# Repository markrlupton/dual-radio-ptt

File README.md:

# Dual-Radio PTT Audio Board (Teensy 4.0): rev C.2

A carrier for a Teensy 4.0 that bridges a headset to two tactical radios. A front-panel daughterboard carries four encoders, the PTT buttons and the LEDs.

Rev C.2 is the manufacturing close-out after the fourth outside review (of rev C.1). That review found no new electrical problem, so **the copper and the circuit are unchanged from C.1** apart from the courtyard fix. This revision covers parts selection, the project footprint library and the fab and assembly files. The full spec is at https://claude.ai/artifact/69VW2KktqLnx2tKRjk1YQv ; its "Rev C", "Rev C.1" and "Rev C.2" sections list every change.

| Board | Size | Stack | Parts | Status |
|---|---|---|---|---|
| `radio_carrier` | 65 × 95 mm | F sig + GND / In1 solid GND / In2 +5.2 V plane (low-current rails and a few codec-area signals) / B sig + GND | 240 | Fully routed. DRC (KiCad 7.0.11): **0 copper, 0 courtyard, 0 unconnected, 0 footprint/library** issues. Only silkscreen warnings are left (silk clipped by mask or overlapping, which JLC clips anyway). ERC: 0 errors, 0 warnings. |
| `radio_frontpanel` | 124 × 38 mm | 4 layers (both inner layers GND) | 54 | Layout unchanged from rev B. DRC: same result as the carrier (silkscreen warnings only). ERC: 0 errors, 0 warnings. |

Vias are 0.45 mm with a 0.2 mm drill on the carrier and 0.5 / 0.25 mm on the front panel. Order the carrier with the **JLC04161H-7628** stack-up and **impedance control** (see below).

## What changed in rev C.2 (fourth review)
| Review item | Rev C.2 |
|---|---|
| **LCSC selections must keep the specified tolerances** (selecting by value and package alone is not enough) | Every SMT row on both boards now has a specific MPN **and** LCSC number, chosen together, in the schematic (`MPN` and `LCSC` fields), both BOMs and the JLC BOM. Precision parts: **15 kΩ 0.1 % 25 ppm** Yageo RT0603BRD0715KL **C326733**; **11 kΩ 0.1 % 25 ppm** FH TD03G1102BT **C667038** (alt Yageo RT0603BRD0711KL); 20 kΩ / 4.99 kΩ 0.1 % unchanged (C723637 / C723532). Rev C.1's note that LCSC lacked 0.1 % 15 k / 11 k was wrong. The JLC BOM's Comment column is now the MPN, so JLC matches on part number, not value. See the selection table below. |
| **A real dielectric error turned up** | The generic 1 nF entry pointed at **C21122, an X7R part**, while C24, C32–C34 and C42–C44 are specified C0G (mic and ADC RF filters, TX low-pass). They are now FH 0603CG102J500NT **C1636** (C0G 50 V 5 %). The generator now refuses to emit a C0G capacitor without a C0G part selected, so this can't recur. |
| **Five power-stage courtyard overlaps** | Fixed: C103 / C104 moved 0.45 mm and C105 / C106 0.3 mm with their tracks. DRC now reports no courtyard overlaps. Switching-loop geometry is effectively unchanged. |
| **Footprint-library warning (codec footprint)** | Every footprint on both boards is now in a **project library** `radio.pretty` with its own `fp-lib-table`. That is 33 footprints on the carrier and 10 on the front panel, U1's HTQFP-64 thermal-via footprint included. All FPIDs in the PCB and all schematic `Footprint` fields point to `radio:<name>`. The library copies were checked pad-for-pad against what is placed on the boards (`mkfplib.py` asserts it). The project no longer depends on the installed KiCad library version; KiCad 8–10 renamed or revised several of these footprints. 3D models still reference the KiCad stock model path, which affects only the 3D view. |
| PCB ↔ schematic link | The PCB footprints now carry their schematic symbols' UUIDs (`relink.py`), so Update-PCB-from-Schematic sees a linked design without "re-link by reference". |
| **Controlled impedance** | Confirmed what we can confirm here: all three pairs are 0.30 mm / 0.20 mm gap on F.Cu only, no vias, over solid In1 GND. Lengths 39.9 / 39.7, 41.5 / 41.3 and 13.5 / 10.1 mm. Computed **89.3 Ω differential with mask** (εr 4.4), 95.9 Ω bare. **Order "Impedance control: yes" with JLC04161H-7628** and put in the order remark: *USB D+/D− pairs (nets USB_A_*, USB_B_*, USBH_*): 90 Ω ±10 % differential, L1 referenced to L2, 0.30 mm trace / 0.20 mm gap.* JLC may adjust width by a few µm to hit target; accept that. Only JLC's coupon measurement confirms the number. |
| **Host cable arrangement** | Stated explicitly under "Things you must do" (item 2) with J3's pinout. The pigtail is the one uncontrolled-impedance section of the high-speed path. |
| **Fab and assembly review** | Gerbers (4 Cu, paste, mask, silk, edge), separate PTH / NPTH Excellon and the job file were regenerated from the C.2 boards. **CPL rotations:** the JLC corrections for KiCad stock footprints are applied: SOT-23/-5/-6 +180°, SOIC / SOP / TSSOP +270°, VQFN-16 +270°. **`*_rotation_check.csv` lists every polarized part** with its KiCad angle, offset, final CPL angle and what to look at for pin 1. Packages the table doesn't cover are left at KiCad's angle and flagged: U1 HTQFP-64, U4 / U11 PVSON-10, U5 SSOP-28, U12 WSON-12, U15 X2QFN-12, Y1, the LEDs, the SOD diodes, J10–J12, J15, SW1. **Check every flagged part in JLC's placement preview before releasing the order**; their preview is the authority because it uses their own footprint for each LCSC part. All parts are top-side. |
| Substitutions | Leave JLC's automatic substitution off. If a part goes out of stock, pick a replacement from the alternates in the MPN field or one of the same tolerance / TCR / dielectric. Never substitute a 0.1 % resistor with a 1 % one, or a C0G with an X7R. |

### Parts chosen in rev C.2 (previously unselected or generic)
| Ref | Value / spec | MPN | LCSC |
|---|---|---|---|
| R70 R72 R75 R77 | 15 kΩ 0.1 % 25 ppm | Yageo RT0603BRD0715KL | C326733 |
| R71 R73 R76 R78 | 11 kΩ 0.1 % 25 ppm | FH TD03G1102BT (alt Yageo RT0603BRD0711KL) | C667038 |
| R116 R117 | 45.3 kΩ 1 % (current limit) | Viking ARG03FTC4532 (thin film, 25 ppm; alt Bourns CR0603-FX-4532ELF C49675646) | C218038 |
| R24 | 169 Ω 1 % (INA217 gain) | Panasonic ERJ-3EKF1690V | C403019 |
| R120 | 910 kΩ 1 % (TUSB321 VBUS_DET) | Bourns CR0603-FX-9103ELF (alt RESI AECR0603F910KK9 C352285) | C203887 |
| R122 | 1.24 kΩ 1 % (BQ24074 ILIM) | Vishay CRCW06031K24FKEA (alt FH RS-03K1241FT C321702) | C843923 |
| R127 | 422 kΩ 1 % (boost FB) | RALEC RTT034223FTP | C103627 |
| R129 | 294 kΩ 1 % (charge-pump FB+) | RALEC RTT032943FTP (alt Vishay CRCW0603294KFKEA C2092132) | C13177 |
| R131 | 287 kΩ 1 % (charge-pump FB−) | LIZ CR0603FA2873G | C100934 |
| C24 C32–C34 C42–C44 | 1 nF C0G | FH 0603CG102J500NT (alt Samsung CL10C102JB8NNNC C163508) | C1636 |
| C29 | 2.7 nF C0G | Walsin 0603N272J500CT | C388043 |
| C60–C63 | 330 pF C0G | Samsung CL10C331JB8NNNC | C1664 |
| C120 | 18 pF C0G | Samsung CL10C180JB8NNNC | C1647 |
| C80 C81 (DNP) | 10 pF C0G | Samsung CL10C100JB8NNNC | C1634 |
| Y1 | 12 MHz 3225, 20 pF, ±10 ppm | YXC X322512MSB4SI | C9002 |
| Front panel D3 | amber / orange 0805 | NationStar NCD0805O1 (605 nm) | C84262 |
| J10 J11 / J12 | JST GH 10 / 6 | BM10B-GHS-TBT / BM06B-GHS-TBT | C2983879 / C189892 |
| J15, SW1, ENC1–4 | USB-C, slide switch, encoders | GCT USB4125-GF-A-0190, C&K PCM12SMTR, Bourns PEC12R-4217F-S0024 | C5246813, C221841, C49671241 |

Rows still without an LCSC number are hand-soldered commodity mechanicals: 1×14 sockets, 1×3 / 2×8 headers, Micro-Fit 43650-0315 and the tactile switches. They are in the JLC BOM so you can mark them DNP. Stock moves; re-check availability in JLC's BOM tool when you order.

## What changed in rev C.1 (third review)
| Review item | Rev C.1 |
|---|---|
| **Battery current path had a 0.2 mm via and a 0.15 mm section feeding U10's BAT pins** | U10 (BQ24074) is turned 180° so its BAT pins face J16 and its OUT pins face the boost stage. **Both high-current paths are now single F.Cu copper pours with no vias:** J16 pin 1 → U10 BAT (narrowest about 1.55 mm along the run, about 1.05 mm only where the copper meets the 0.5 mm-pitch QFN pins) and U10 OUT → L1 / C103 / C104 / U11 VIN (narrowest about 1.1 mm, about 0.95 mm at the pin row). Other nets are kept out of both pours by the router, and no via of any net may sit within about 0.5 mm of their edges. C102 (battery cap) now sits on the battery pour under J16; C100 (IN cap) sits right under U10's IN pin; C101 moved near SW1. |
| USB-C input path | VBUS_IN (≤1.3 A) runs 0.5 mm (one 0.25 mm neck at the A9 pin between the CC pins). Each layer change uses two vias in parallel: two 0.6/0.3 mm vias going down, one 0.6/0.3 mm plus one 0.5/0.25 mm via coming up at U10's IN pin. Power-net vias are 0.6/0.3 mm wherever they fit. |
| **J16 pin 2 (battery −) thermal relief: 1 spoke where 2 are required** | J16, U10, C101 and C102 ground pads now connect solidly to the pours (no thermal relief). |
| **Current limit did not guarantee 500 mA with a 1 % resistor** | R116 / R117 → **45.3 kΩ 1 %**. TI's equations with the resistor tolerance included give **0.519 A minimum (R +1 %)** and **0.644 A maximum (R −1 %)** per port. 47.5 kΩ gave 0.494–0.616 A. |
| Host USB pair had 0.15 mm segments | Those were pad-entry stubs inside J3's 1.7 mm pads; they are now 0.30 mm like the rest of the pair. The pair's breakout into J3 is still uncoupled over the 2.54 mm pin pitch. |
| **"About 93 Ω under mask" was not what the solver modelled** | `zdiff.py --mask` now models the solder mask with JLCPCB's figures (1.2 mil on laminate and between traces, 0.6 mil on copper, εr 3.8) and 1.6 mil finished outer copper. 0.30 / 0.20 mm on the 0.2104 mm 7628 prepreg: **95.9 Ω bare, 89.3 Ω with mask** (εr 4.4), 94.3 / 87.9 Ω at εr 4.6. Rectangular trace cross-section; trapezoidal etching raises it slightly. Have JLC confirm with impedance control ordered. |
| **ERC not clean** | KiCad's own ERC (7.0.11, run in the schematic editor) now reports **0 errors and 0 warnings on both boards**. Fixes: PWR_FLAGs only on nets nothing else drives (GND, VBUS_IN, +5V_TEENSY), U11's second VOUT pin made passive, LM27762 PGOOD tied to GND as its datasheet says for unused (pin typed passive), PCM3168A pin 44 typed as the input it is in I²C mode, no stray no-connect flags, a project symbol library (`lib.kicad_sym` + `sym-lib-table`) so no library warnings. Reports: `*-erc.rpt`. Newer KiCad versions add checks; I could not run KiCad 10 here. |
| LCSC numbers | Added: TPS61230DRCR C139626, NCP163ASN500T1G C603657, TUSB321RWBR C139392, PESD5V0L1BA C85380, SMF15CA C2890424, L1 → XAL4020-102MEC C4555951 (current version of the -MEB), RT0603BRD0720KL C723637, RT0603BRD074K99L C723532. |

## What changed from rev B (rev C)
| Review item | Rev C |
|---|---|
| **U6 / U7 enable polarity wrong** (TPS2051B is active-high; the hub's PWRJ is active-low) | Replaced with **TPS2552DBVR**: active-low EN, open-drain FAULT, adjustable current limit. EN ← HUB_PWRJ, FAULT → HUB_OVC (wired-OR). |
| Port current limit 0.75–1.25 A per port (TPS2051B) | R116 / R117 on ILIM set the limit (rev C.1: 45.3 kΩ, **0.519–0.644 A per port** including the 1 % tolerance). Two shorted ports can't pull more than about 1.3 A from +5V2. |
| **J16 JST-PH (2 A) on a 2.6 A battery path** | **Molex Micro-Fit 3.0 43650-0315** vertical (5 A per contact): 1 +, 2 −, 3 NTC. Mating housing 43645-0300 with 43030 crimps. |
| Battery / SYS copper | Superseded in rev C.1 by the battery and SYS pours above. |
| **USB pairs not coupled / not single-layer** | All three pairs re-routed **on F.Cu only, no vias, one width**: 0.30 mm traces, 0.20 mm gap (0.50 mm pitch) over the solid In1 GND, routed as a true pair (one centreline, both conductors offset from it). Impedance: see the rev C.1 table (89 Ω with mask modelled, target 90 Ω). Measured lengths: radio A 39.9 / 39.7 mm, radio B 41.5 / 41.3 mm (0.2 mm skew); host link 13.5 / 10.1 mm (set by J3's 2.54 mm pin spacing). |
| Pair topology | To route both radio pairs without crossing, the hub ports were swapped (radio A now on FE1.1s port 2, pins 8 / 9; radio B on port 1, pins 10 / 11) and U8 / U9 were turned 180° so each pair flows straight through its USBLC6 (pins 1→6 and 3→4) before dropping into the connector. The ESD ground pin gets its own via under the part. |
| Continuous load vs. 1.3 A USB input | Operating-mode table below. At full load on USB the battery supplements; this is intentional and stated. |
| PTT TVS (SMF15CA, 15 V standoff) | Maximum radio PTT keying voltage is now a stated limit: **≤ 15 V open-circuit**. |
| Port power cycling | Documented: the hub's power switching is ganged, so a power-cycle drops **both** radio ports. |

## Operating modes and power budget
Loads at the +5.2 V boost output: board ≈ 350 mA (1.8 W); each radio port 0–500 mA nominal, current-limited at 0.519 A min / 0.644 A max.

| Mode | Input available | Full load (board + 2 × 500 mA ≈ 7 W out, ≈ 7.8 W in) | Board only (≈ 2 W in) |
|---|---|---|---|
| Battery only | 18650, 3.0–4.2 V | ≈ 2.2 A from the cell at 3.6 V, ≈ 2.6 A at 3.0 V. Use a cell rated ≥ 5 A continuous. | ≈ 0.6 A from the cell |
| USB-C, source offers ≥ 1.5 A (TUSB321 → 1.3 A input limit) | ≈ 6 W | Input covers most of it; the battery supplies the rest (BQ24074 supplement mode). The cell slowly discharges. | Fully covered; battery charges |
| USB-C, default 500 mA source | ≈ 2.5 W | Battery supplies ≈ 5 W; net discharge | Covered, little or no charge current |
| Fault: both ports shorted | — | ≤ 2 × 0.644 A ≈ 6.7 W + board ≈ 8.5 W out, ≈ 9.7 W in → ≤ 3.2 A from the cell at 3.0 V (2.7 A at 3.6 V). Within the TPS61230 (4 A valley), BQ24074 battery FET (4.5 A) and Micro-Fit (5 A) ratings, and carried by the no-via battery/SYS pours. The TPS2552s thermally cycle into a hard short and report FAULT to the hub. | — |

**Without a battery fitted, full radio-port load on USB alone is not supported.**

## Things you must do
1. **Cut the Teensy VUSB–VIN pad.**
2. **USB host pigtail (J3).** J3 pin 1 = D+ (USBH_DP), pin 2 = D− (USBH_DM), pin 3 = GND. Wire the Teensy 4.0's underside USB-host D+ / D− pads to J3 pins 1 / 2, and a Teensy GND pin to J3 pin 3. Use a twisted pair (about 1 twist per cm, **60 mm or less**, 28–30 AWG), with the GND wire twisted along with it or run right beside it. This hop carries the hub's high-speed upstream link (480 Mb/s). It is the only part of that path without controlled impedance, so keep it as short as the stack-up allows and don't route it past the boost inductor L1. If the hub shows enumeration errors, shorten the pigtail first.
3. **Firmware is not written yet.** Everything below is a requirement on firmware you still need to write:
   - Codec rate: set PCM3168A **SRAD = SRDA = 01 (single rate)**; auto mode reads 256 fs MCLK as dual rate. Set FMTAD / FMTDA to match the Teensy's TDM slot layout.
   - PTT safety: watchdog, transmit timeout, release PTT if I²C to the buttons stalls. The gate pull-downs only cover reset.
   - Headphone mute: HP_EN high only after the codec and rails are running; low before shutdown.
   - Port power: a stuck radio is recovered by the USB host toggling hub port power, which cycles both ports together.
4. **Battery.** Protected 18650 with a 10 kΩ NTC on J16 pin 3 (or fit R124, which disables temperature protection).
5. **Radios.** PTT line must be ≤ 15 V open-circuit and switched to ground. RX ≤ 2 Vrms differential line level (fit R34 / R54 for speaker level). TX is mic level; R40 / R60 (100 Ω) set the drive level and may need changing per radio. Compatibility with a specific radio is conditional on these until checked against its pinout.

## Codec channel map (TDM slots)
| Channel | Use |
|---|---|
| ADC1 | Aux in (J14 pins 9 / 10) |
| ADC2, ADC6 | Unused (terminated) |
| ADC3 | Headset mic (INA217, G ≈ 60) |
| ADC4 / ADC5 | Radio A / Radio B RX |
| DAC1 / DAC2 | Headset L / R (OPA1622) |
| DAC3 / DAC4 | Radio A / Radio B TX (OPA1678) |
| DAC5 | Aux out (J14 pins 13 / 14) |

## Teensy 4.0 pin map
| Pin | Signal | | Pin | Signal |
|---|---|---|---|---|
| 0 | EXP_0 (aux) | | 23 | MCLK |
| 1 | EXP_1 (aux) | | 22 | VBAT_SENSE (A8, ½ divider) |
| 2 | PTT_A drive | | 21 | BCLK |
| 3 | PTT_B drive | | 20 | FSYNC |
| 4 | IOX_INT (TCA9555) | | 19 / 18 | I²C SCL / SDA |
| 5 | CODEC_RST | | 17 / 16 | ENC Radio-A channel B / A |
| 6 | HP_EN | | 15 / 14 | ENC Radio-A volume B / A |
| 7 / 8 | TDM TX / RX | | 13 | EXP_13 (aux) |
| 9 / 10 | ENC Radio-B volume A / B | | VIN | +5 V via B5819W |
| 11 / 12 | ENC Radio-B channel A / B | | 3V3 | not used |

## Connectors
| Ref | Part | Pins |
|---|---|---|
| J10 / J11 | JST-GH 10 | 1 RX, 2 RX_RTN, 3 TX, 4 TX_RTN, 5 PTT (≤ 15 V), 6 PTT_RTN, 7 D+, 8 D−, 9 VBUS (switched, 0.519–0.644 A limit), 10 GND |
| J12 | JST-GH 6 | 1 MIC+, 2 MIC−, 3 SPK_L, 4 SPK_R, 5 GND, 6 shield |
| J13 | 2×8 1.27 mm | front-panel ribbon |
| J14 | 2×8 2.54 mm aux | +3V3, +5V2, EXP_0/1/13, ADC1±, DAC5±, GND |
| J15 | USB-C | power in (TUSB321 detects the source's current) |
| J16 | Molex Micro-Fit 3.0 43650-0315 | 1 +, 2 −, 3 NTC |
| J3 | 1×3 | USB host D+, D−, GND pigtail |

## Known limits
- **Ground isolation:** none. The radio ports share ground through J10 / J11 pin 10 and USB.
- **CPL rotations** for packages not in the standard correction table are KiCad's own angle; confirm them in JLC's placement preview (`*_rotation_check.csv`).
- **Moved parts:** C80 (DNP crystal load cap) moved 5 mm from the crystal to clear the USB corridor. Leave it unfitted (the FE1.1s has internal load capacitors). C94 (radio B VBUS bulk) moved next to U7.
- **USB impedance:** computed, not measured. Order impedance control and let JLC confirm.
- **Charge-status LED feed:** R125's VBUS_IN branch and the battery-voltage sense branch (VBAT to R9 / TP15) are thin tracks with single vias; they carry milliamps.

## Files
- `radio_carrier/` and `radio_frontpanel/`: KiCad 7 projects (open with KiCad 7 or newer) with their project symbol library (`lib.kicad_sym`, `sym-lib-table`), project footprint library (`radio.pretty`, `fp-lib-table`), and ERC / DRC reports.
- `*/fab/`: Gerbers and drill (zip), `*_BOM_JLC.csv`, `*_CPL_JLC.csv` (JLC rotation corrections applied), `*_rotation_check.csv`, `*_BOM_full.csv` (MPN, LCSC, fitted, SMT / hand-solder), schematic PDF.
- `img/`: renders.
- `scripts/`: generators, router and finishing scripts, `zdiff.py` impedance solver (`--mask`), `pourcheck.py` (narrowest copper on the power paths), `erc_gui.sh` (runs KiCad's ERC headless), `mkfplib.py` (builds the project footprint library and checks it against the boards), `relink.py` (PCB ↔ schematic UUID link).
- `img/carrier_power_paths.png`, `img/carrier_usb_pairs.png`: the power pours and the USB pairs.

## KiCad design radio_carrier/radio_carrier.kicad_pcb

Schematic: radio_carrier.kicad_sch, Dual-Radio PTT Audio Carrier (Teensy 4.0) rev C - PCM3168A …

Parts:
C1, C25, C26, C50, C51, C65, C66, C82, C84, C86, C88, C90, C93: 100nF; C_0603_1608Metric; MPN 0603 X7R 16V; LCSC C14663
C10, C11, C12, C13, C14, C15, C23, C28, C30, C31, C40, C41, C70, C71, C72, C109, C111, C115, C117, C118, C119: 1uF; C_0603_1608Metric; MPN 0603 X7R 16V; LCSC C15849
C16, C17, C18, C19, C20, C21, C22, C27, C35, C45, C67, C68, C83, C85, C87, C91, C94, C101, C102, C104, C110, C112: 10uF; C_0805_2012Metric; MPN 0805 X7R 16V; LCSC C15850
C24, C32, C33, C34, C42, C43, C44: 1nF; C_0603_1608Metric; MPN FH 0603CG102J500NT (C0G 50V 5%; alt Sam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; LCSC C1636
C29: 2.7nF; C_0603_1608Metric; MPN Walsin 0603N272J500CT (C0G 50V 5%); LCSC C388043
C60, C61, C62, C63: 330pF; C_0603_1608Metric; MPN Samsung CL10C331JB8NNNC (C0G 50V 5%); LCSC C1664
C80, C81: 10pF; C_0603_1608Metric; MPN Samsung CL10C100JB8NNNC (C0G 50V 5%); LCSC C1634; not fitted
C100, C116: 4.7uF; C_0805_2012Metric; MPN 0805 X7R 16V; LCSC C1779
C103, C105, C106, C107: 22uF; C_0805_2012Metric; MPN 0805 X7R 16V; LCSC C45783
C108: 10nF; C_0603_1608Metric; MPN 0603 X7R 16V; LCSC C57112
C113, C114: 2.2uF; C_0603_1608Metric; MPN 0603 X7R 16V; LCSC C23630
C120: 18pF; C_0603_1608Metric; MPN Samsung CL10C180JB8NNNC (C0G 50V 5%); LCSC C1647
D1: B5819W; D_SOD-123; MPN B5819W Schottky 1 A 40 V; LCSC C8598
D2, D3: BAV99; SOT-23; MPN BAV99 dual diode; LCSC C2500
D10, D11, D12, D20, D21, D22: PESD5V0L1BA; D_SOD-323; MPN Nexperia PESD5V0L1BA bidirectional; LCSC C85380
D13, D23: SMF15CA; D_SOD-123F; MPN SMF15CA bidirectional TVS (VRWM 15 V, V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; LCSC C2890424
D30: SMF5.0A; D_SOD-123F; MPN SMF5.0A TVS 5 V; LCSC C78395
D31: RED; LED_0805_2012Metric; MPN 0805 red LED; LCSC C84256
D32: GREEN; LED_0805_2012Metric; MPN 0805 green LED; LCSC C2297
H1, H2, H3, H4: M2.5; MountingHole_2.7mm_M2.5
J1: Teensy 4.0 left (GND,0..12); PinSocket_1x14_P2.54mm_Vertical; MPN 1x14 2.54 mm female socket
J2: Teensy 4.0 right (VIN,GND,3V3,23..13); PinSocket_1x14_P2.54mm_Vertical; MPN 1x14 2.54 mm female socket
J3: USB HOST (wire to Teensy pads); PinHeader_1x03_P2.54mm_Vertical; MPN 1x3 2.54 mm header
J10: RADIO A (JST-GH 10); JST_GH_BM10B-GHS-TBT_1x10-1MP_P1.25mm_Vertical; MPN JST BM10B-GHS-TBT; LCSC C2983879
J11: RADIO B (JST-GH 10); JST_GH_BM10B-GHS-TBT_1x10-1MP_P1.25mm_Vertical; MPN JST BM10B-GHS-TBT; LCSC C2983879
J12: HEADSET (JST-GH 6); JST_GH_BM06B-GHS-TBT_1x06-1MP_P1.25mm_Vertical; MPN JST BM06B-GHS-TBT; LCSC C189892
J13: FRONT PANEL (2x8 1.27); PinHeader_2x08_P1.27mm_Vertical; MPN 2x8 1.27 mm header
J14: AUX (2x8 2.54); PinHeader_2x08_P2.54mm_Vertical; MPN 2x8 2.54 mm header
J15: USB-C 5V IN; USB_C_Receptacle_GCT_USB4125-xx-x-0190_6P_TopMnt_Horizontal; MPN GCT USB4125-GF-A-0190 (power only); LCSC C5246813
J16: 18650 + NTC (Micro-Fit 3.0); Molex_Micro-Fit_3.0_43650-0315_1x03_P3.00mm_Vertical; MPN Molex 43650-0315 Micro-Fit 3.0 vertical
K1, K2: AQY212GS; SOP-4_3.8x4.1mm_P2.54mm; MPN Panasonic AQY212GS PhotoMOS; LCSC C719745
L1: 1.0uH; L_Coilcraft_XAL4020-XXX; MPN Coilcraft XAL4020-102MEC (1.0 uH, Isat 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; LCSC C4555951
Q1, Q2, Q3: 2N7002; SOT-23; MPN 2N7002 N-MOSFET; LCSC C8545
R1, R2, R3, R4, R5: 33; R_0603_1608Metric; MPN 0603 1% resistor; LCSC C23140
R6, R7, R133: 2.2k; R_0603_1608Metric; MPN 0603 1% resistor; LCSC C4190
R8, R22, R23, R30, R31, R50, R51, R90, R91, R111, R113, R114, R115: 10k; R_0603_1608Metric; MPN 0603 1% resistor; LCSC C25804
R9, R10, R26, R27, R32, R33, R43, R52, R53, R63, R80, R92, R93, R121, R128, R130, R132, R134: 100k; R_0603_1608Metric; MPN 0603 1% resistor; LCSC C25803
R20, R21: 47; R_0603_1608Metric; MPN 0603 1% resistor; LCSC C23182
R24: 169; R_0603_1608Metric; MPN Panasonic ERJ-3EKF1690V (1%, 100 ppm); LCSC C403019
R25: DNP; R_0603_1608Metric; MPN not fitted; not fitted
R28, R39, R42, R59, R62, R123, R125: 1k; R_0603_1608Metric; MPN 0603 1% resistor; LCSC C21190
R34, R54: 2.2k; R_0603_1608Metric; MPN 0603 1% resistor; LCSC C4190; not fitted
R35, R37, R55, R57: 20k; R_0603_1608Metric; MPN Yageo RT0603BRD0720KL (0.1%, 25 ppm); LCSC C723637
R36, R38, R56, R58: 4.99k; R_0603_1608Metric; MPN Yageo RT0603BRD074K99L (0.1%, 25 ppm); LCSC C723532
R40, R60, R102, R103: 100; R_0603_1608Metric; MPN 0603 1% resistor; LCSC C22775
R41, R61, R74, R79: 10; R_0603_1608Metric; MPN 0603 1% resistor; LCSC C22859
R44, R64: 330; R_0603_1608Metric; MPN 0603 1% resistor; LCSC C23138
R45, R65, R81: 0; R_0603_1608Metric; MPN 0603 1% resistor; LCSC C21189
R70, R72, R75, R77: 15k; R_0603_1608Metric; MPN Yageo RT0603BRD0715KL (0.1%, 25 ppm); LCSC C326733
R71, R73, R76, R78: 11k; R_0603_1608Metric; MPN FH TD03G1102BT (0.1%, 25 ppm; alt Yageo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; LCSC C667038
R110: 2.7k; R_0603_1608Metric; MPN 0603 1% resistor; LCSC C13167
R112: 4.7k; R_0603_1608Metric; MPN 0603 1% resistor; LCSC C23162
R116, R117: 45.3k; R_0603_1608Metric; MPN Viking ARG03FTC4532 (1% thin film, 25 p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; LCSC C218038
R120: 910k; R_0603_1608Metric; MPN Bourns CR0603-FX-9103ELF (1%; alt RESI 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; LCSC C203887
R122: 1.24k; R_0603_1608Metric; MPN Vishay CRCW06031K24FKEA (1%; alt FH RS-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; LCSC C843923
R124: 10k; R_0603_1608Metric; MPN 0603 1% resistor; LCSC C25804; not fitted
R126: 1M; R_0603_1608Metric; MPN 0603 1% resistor; LCSC C22935
R127: 422k; R_0603_1608Metric; MPN RALEC RTT034223FTP (1%); LCSC C103627
R129: 294k; R_0603_1608Metric; MPN RALEC RTT032943FTP (1%; alt Vishay CRCW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; LCSC C13177
R131: 287k; R_0603_1608Metric; MPN LIZ CR0603FA2873G (1%); LCSC C100934
SW1: POWER; SW_SPDT_PCM12; MPN C&K PCM12SMTR slide switch; LCSC C221841
TP1: MCLK; TestPoint_Pad_D1.0mm; MPN test point
TP2: BCLK; TestPoint_Pad_D1.0mm; MPN test point
TP3: FSYNC; TestPoint_Pad_D1.0mm; MPN test point
TP4: TDM_TX; TestPoint_Pad_D1.0mm; MPN test point
TP5: TDM_RX; TestPoint_Pad_D1.0mm; MPN test point
TP6: RST; TestPoint_Pad_D1.0mm; MPN test point
TP7: +5V2; TestPoint_Pad_D1.0mm; MPN test point
TP8: +3V3; TestPoint_Pad_D1.0mm; MPN test point
TP9: +5VA; TestPoint_Pad_D1.0mm; MPN test point
TP10: +5VP; TestPoint_Pad_D1.0mm; MPN test point
TP11: PTT_A; TestPoint_Pad_D1.0mm; MPN test point
TP12: PTT_B; TestPoint_Pad_D1.0mm; MPN test point
TP13: -5VP; TestPoint_Pad_D1.0mm; MPN test point
TP14: SYS; TestPoint_Pad_D1.0mm; MPN test point
TP15: VBAT; TestPoint_Pad_D1.0mm; MPN test point
TP16, TP17: GND; TestPoint_Pad_D1.0mm; MPN test point
U1: PCM3168APAPR; HTQFP-64-1EP_10x10mm_P0.5mm_EP8x8mm_Mask4.4x4.4mm_ThermalVi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; MPN TI PCM3168APAPR; LCSC C529289
U2: INA217AIDWR; SOIC-16W_7.5x10.3mm_P1.27mm; MPN TI INA217AIDWR; LCSC C1849416
U3: OPA1678IDR; SOIC-8_3.9x4.9mm_P1.27mm; MPN TI OPA1678IDR; LCSC C192421
U4: OPA1622IDRCR; Texas_S-PVSON-N10; MPN TI OPA1622IDRCR; LCSC C2876559
U5: FE1.1S-BSOP28BCN; SSOP-28_3.9x9.9mm_P0.635mm; MPN Terminus FE1.1S-BSOP28BCN; LCSC C9359
U6, U7: TPS2552DBVR; SOT-23-6; MPN TI TPS2552DBVR adjustable limit, ACTIVE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; LCSC C46506
U8, U9: USBLC6-2SC6; SOT-23-6; MPN ST USBLC6-2SC6; LCSC C7519
U10: BQ24074RGTR; VQFN-16-1EP_3x3mm_P0.5mm_EP1.6x1.6mm_ThermalVias; MPN TI BQ24074RGTR; LCSC C54313
U11: TPS61230DRCR; Texas_S-PVSON-N10_ThermalVias; MPN TI TPS61230DRCR; LCSC C139626
U12: LM27762DSSR; WSON-12-1EP_3x2mm_P0.5mm_EP1x2.65_ThermalVias; MPN TI LM27762DSSR; LCSC C473398
U13: NCP163ASN500T1G; SOT-23-5; MPN onsemi NCP163ASN500T1G; LCSC C603657
U14: TLV75533PDBVR; SOT-23-5; MPN TI TLV75533PDBVR; LCSC C404027
U15: TUSB321RWBR; Texas_X2QFN-12_1.6x1.6mm_P0.4mm; MPN TI TUSB321RWBR; LCSC C139392
Y1: 12MHz; Crystal_SMD_3225-4Pin_3.2x2.5mm; MPN YXC X322512MSB4SI (12 MHz 3225, 20 pF, 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; LCSC C9002

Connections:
+3V3: C14.1, C15.1, C18.1, C118.1, J13.1, J13.2, J14.1, R6.1, R7.1, R8.1, R44.1, R64.1, TP8.1, U1.12 (VDD2), U1.46 (VDD1), U14.5 (OUT)
+5V2: C83.1, C84.1, C90.1, C93.1, C105.1, C106.1, C107.1, C109.1, C110.1, C115.1, C117.1, C120.1, D1.2 (A), J14.2, R112.1, R127.1, R133.1, TP7.1, U5.20 (VDD5), U6.1 (IN), U7.1 (IN), U11.3 (VOUT), U11.4 (VOUT), U12.3 (VIN), U12.8 (EN-), U12.12 (EN+), U13.1 (IN), U13.3 (EN), U14.1 (IN), U14.3 (EN)
+5VA: C10.1, C11.1, C12.1, C13.1, C16.1, C17.1, C116.1, TP9.1, U1.3 (VCCAD2), U1.14 (VCCDA1), U1.34 (VCCDA2), U1.49 (VCCAD1), U13.5 (OUT)
+5VP: C25.1, C50.1, C65.1, C67.1, C113.1, D2.2 (K2), D3.2 (K2), R129.1, TP10.1, U2.13 (V+), U3.8 (V+), U4.2 (V+), U12.11 (OUT+)
+5V_TEENSY: D1.1 (K), J2.1 (VIN)
-5VP: C26.1, C51.1, C66.1, C68.1, C114.1, D2.1 (A1), D3.1 (A1), R131.1, TP13.1, U2.7 (V-), U3.4 (V-), U4.4 (V-), U4.11 (EP(V-)), U12.6 (OUT-)
ADC1_N: R91.2, R93.1, U1.51 (VIN1-)
ADC1_P: R90.2, R92.1, U1.52 (VIN1+)
ADC2: C72.1, U1.53 (VIN2-), U1.54 (VIN2+)
ADC3_N: C28.1, C29.2, R27.1, U1.55 (VIN3-)
ADC3_P: C29.1, R26.1, R28.2, U1.56 (VIN3+)
ADC4_N: C32.2, R31.2, R33.1, R34.2, U1.57 (VIN4-)
ADC4_P: C32.1, R30.2, R32.1, R34.1, U1.58 (VIN4+)
ADC5_N: C42.2, R51.2, R53.1, R54.2, U1.61 (VIN5-)
ADC5_P: C42.1, R50.2, R52.1, R54.1, U1.62 (VIN5+)
ADC6: C23.1, U1.63 (VIN6-), U1.64 (VIN6+)
AUX_ADC1_N: C71.1, J14.10
AUX_ADC1_N_C: C71.2, R91.1
AUX_ADC1_P: C70.1, J14.9
AUX_ADC1_P_C: C70.2, R90.1
AUX_DAC5_N: J14.14, R103.2
AUX_DAC5_P: J14.13, R102.2
BB_FB: C120.2, R127.2, R128.1, U11.7 (FB)
BB_SS: C108.1, U11.6 (SS)
BB_SW: L1.2, U11.1 (SW), U11.2 (SW)
CC1: J15.A5 (CC1), U15.1 (CC1)
CC2: J15.B5 (CC2), U15.2 (CC2)
CC_HI_N: Q3.1 (G), R121.2, U10.6 (EN1), U15.7 (OUT1)
CC_VDET: R120.2, U15.5 (VBUS_DET)
CHG_EN2: Q3.3 (D), R134.2, U10.5 (EN2)
CHG_ILIM: R122.1, U10.12 (ILIM)
CHG_ISET: R123.1, U10.16 (ISET)
CHG_LED_A: D31.2 (A), R125.2
CHG_LED_K: D31.1 (K), U10.9 (~CHG)
CHG_TS: J16.3, R124.1, U10.1 (TS)
CODEC_RST: J1.7 (5), TP6.1, U1.4 (~RST)
CP_C1N: C111.2, U12.9 (C1-)
CP_C1P: C111.1, U12.10 (C1+)
CP_FBN: R131.2, R132.1, U12.7 (FB-)
CP_FBP: R129.2, R130.1, U12.2 (FB+)
CP_OUT: C112.1, U12.5 (CP)
DAC1_N: R70.1, U1.32 (VOUT1-)
DAC1_P: R72.1, U1.31 (VOUT1+)
DAC2_N: R75.1, U1.30 (VOUT2-)
DAC2_P: R77.1, U1.29 (VOUT2+)
DAC3_N: R35.1, U1.28 (VOUT3-)
DAC3_P: R37.1, U1.27 (VOUT3+)
DAC4_N: R55.1, U1.26 (VOUT4-)
DAC4_P: R57.1, U1.25 (VOUT4+)
DAC5_N: R103.1, U1.24 (VOUT5-)
DAC5_P: R102.1, U1.23 (VOUT5+)
ENC_AC_A: J2.11 (16), J13.11
ENC_AC_B: J2.10 (17), J13.12
ENC_AV_A: J2.13 (14), J13.9
ENC_AV_B: J2.12 (15), J13.10
ENC_BC_A: J1.13 (11), J13.15
ENC_BC_B: J1.14 (12), J13.16
ENC_BV_A: J1.11 (9), J13.13
ENC_BV_B: J1.12 (10), J13.14
EXP_0: J1.2 (0), J14.5
EXP_1: J1.3 (1), J14.6
EXP_13: J2.14 (13), J14.8
GND: C1.2, C10.2, C11.2, C12.2, C13.2, C14.2, C15.2, C16.2, C17.2, C18.2, C19.2, C20.2, C21.2, C22.2, C23.2, C25.2, C26.2, C28.2, C34.2, C44.2, C50.2, C51.2, C61.2, C63.2, C65.2, C66.2, C67.2, C68.2, C72.2, C80.2, C81.2, C82.2, C83.2, C84.2, C85.2, C86.2, C87.2, C88.2, C90.2, C91.2, C93.2, C94.2, C100.2, C101.2, C102.2, C103.2, C104.2, C105.2, C106.2, C107.2, C108.2, C109.2, C110.2, C112.2, C113.2, C114.2, C115.2, C116.2, C117.2, C118.2, C119.2, D10.2, D11.2, D12.2, D20.2, D21.2, D22.2, D30.2 (A), D32.1 (K), J1.1 (GND), J2.2 (GND), J3.3, J10.10, J10.MP, J11.10, J11.MP, J12.5, J12.MP, J13.3, J13.4, J13.8, J14.3, J14.4, J14.7, J14.11, J14.12, J14.15, J14.16, J15.A12 (GND), J15.B12 (GND), J15.S1 (SHIELD), J16.2, Q1.2 (S), Q2.2 (S), Q3.2 (S), R10.2, R22.2, R23.2, R38.2, R41.2, R43.2, R45.2, R58.2, R61.2, R63.2, R65.2, R73.2, R78.2, R80.2, R81.2, R110.2, R113.2, R116.2, R117.2, R122.2, R123.2, R124.2, R126.2, R128.2, R130.2, R132.2, TP16.1, TP17.1, U1.2 (AGNDAD2), U1.11 (DGND2), U1.16 (AGNDDA1), U1.33 (AGNDDA2), U1.38 (DIN2), U1.39 (DIN3), U1.40 (DIN4), U1.44 (MDO/ADR1/MD1), U1.45 (MS/ADR0/MD0), U1.47 (DGND1), U1.48 (MODE), U1.50 (AGNDAD1), U1.65 (EP), U2.10 (REF), U4.3 (GND), U5.1 (VSS), U6.2 (GND), U7.2 (GND), U8.2 (GND), U9.2 (GND), U10.4 (~CE), U10.8 (VSS), U10.17 (EP), U11.11 (GND), U12.1 (PGOOD), U12.4 (GND), U12.13 (EP), U13.2 (GND), U14.2 (GND), U15.3 (CURRENT_MODE), U15.4 (PORT), U15.10 (GND), Y1.2 (GND), Y1.4 (GND)
HPA_INV: C60.1, R70.2, R71.1, U4.10 (-INA)
HPA_NI: C61.1, R72.2, R73.1, U4.1 (+INA)
HPA_OUT: C60.2, R71.2, R74.1, U4.9 (OUTA)
HPB_INV: C62.1, R75.2, R76.1, U4.6 (-INB)
HPB_NI: C63.1, R77.2, R78.1, U4.5 (+INB)
HPB_OUT: C62.2, R76.2, R79.1, U4.7 (OUTB)
HP_EN: J1.8 (6), R80.1, U4.8 (EN)
HS_MIC_N: J12.2, R21.1
HS_MIC_P: J12.1, R20.1
HS_SHLD: J12.6, R81.1
HS_SPK_L: J12.3, R74.2
HS_SPK_R: J12.4, R79.2
HUB_1V8: C87.1, C88.1, U5.12 (VD18_O), U5.28 (VD18)
HUB_3V3: C85.1, C86.1, R111.1, R114.1, R115.1, U5.13 (VD33), U5.19 (BUSJ), U5.21 (VD33_O)
HUB_OVC: R114.2, U5.26 (OVCJ), U6.4 (~FAULT), U7.4 (~FAULT)
HUB_PWRJ: R115.2, U5.25 (PWRJ), U6.3 (~EN), U7.3 (~EN)
HUB_REXT: R110.1, U5.14 (REXT)
HUB_RST: C82.1, R111.2, U5.17 (~XRSTJ)
HUB_VBM: R112.2, R113.1, U5.18 (VBUSM)
HUB_XI: C80.1, U5.3 (XIN), Y1.1
HUB_XO: C81.1, U5.2 (XOUT), Y1.3
I2C_SCL: J2.8 (19), J13.6, R7.2, U1.42 (MC/SCL/FMT)
I2C_SDA: J2.9 (18), J13.5, R6.2, U1.43 (MDI/SDA/DEMP)
INA_RG1: R24.1, R25.1, U2.2 (RG1)
INA_RG2: R24.2, R25.2, U2.15 (RG2)
IOX_INT: J1.6 (4), J13.7, R8.2
MIC_AC: C27.2, R28.1
MIC_N_F: C24.2, D3.3 (K1/A2), R21.2, R23.1, U2.4 (VIN-)
MIC_PRE: C27.1, U2.11 (VOUT)
MIC_P_F: C24.1, D2.3 (K1/A2), R20.2, R22.1, U2.5 (VIN+)
PTT_A_DRV: J1.4 (2), R42.1, TP11.1
PTT_B_DRV: J1.5 (3), R62.1, TP12.1
PWR_EN: R126.1, SW1.2 (COM), U11.9 (EN)
PWR_LED_A: D32.2 (A), R133.2
RA_ILIM: R116.1, U6.5 (ILIM)
RA_PTT: D13.1, J10.5, K1.4 (D)
RA_PTTR: D13.2, J10.6, K1.3 (D)
RA_PTT_G: Q1.1 (G), R42.2, R43.1
RA_PTT_K: K1.2 (LED K), Q1.3 (D)
RA_PTT_LED: K1.1 (LED A), R44.2
RA_RX: C30.1, D10.1, J10.1
RA_RXR: C31.1, D11.1, J10.2
RA_RXR_C: C31.2, R31.1
RA_RX_C: C30.2, R30.1
RA_TX: C35.2, D12.1, J10.3
RA_TXR: J10.4, R40.2, R41.1, R45.1
RA_TX_A: C35.1, R39.2, R40.1
RA_TX_INV: C33.1, R35.2, R36.1, U3.2 (-INA)
RA_TX_NI: C34.1, R37.2, R38.1, U3.3 (+INA)
RA_TX_OUT: C33.2, R36.2, R39.1, U3.1 (OUTA)
RA_VBUS: C91.1, J10.9, U6.6 (OUT), U8.5 (VBUS)
RB_ILIM: R117.1, U7.5 (ILIM)
RB_PTT: D23.1, J11.5, K2.4 (D)
RB_PTTR: D23.2, J11.6, K2.3 (D)
RB_PTT_G: Q2.1 (G), R62.2, R63.1
RB_PTT_K: K2.2 (LED K), Q2.3 (D)
RB_PTT_LED: K2.1 (LED A), R64.2
RB_RX: C40.1, D20.1, J11.1
RB_RXR: C41.1, D21.1, J11.2
RB_RXR_C: C41.2, R51.1
RB_RX_C: C40.2, R50.1
RB_TX: C45.2, D22.1, J11.3
RB_TXR: J11.4, R60.2, R61.1, R65.1
RB_TX_A: C45.1, R59.2, R60.1
RB_TX_INV: C43.1, R55.2, R56.1, U3.6 (-INB)
RB_TX_NI: C44.1, R57.2, R58.1, U3.5 (+INB)
RB_TX_OUT: C43.2, R56.2, R59.1, U3.7 (OUTB)
RB_VBUS: C94.1, J11.9, U7.6 (OUT), U9.5 (VBUS)
SYS: C101.1, C103.1, C104.1, L1.1, SW1.1 (A), TP14.1, U10.10 (OUT), U10.11 (OUT), U11.10 (VIN)
TDM_BCLK: R2.2, TP2.1, U1.7 (BCKAD), U1.36 (BCKDA)
TDM_BCLK_T: J2.6 (21), R2.1
TDM_FSYNC: R3.2, TP3.1, U1.6 (LRCKAD), U1.35 (LRCKDA)
TDM_FSYNC_T: J2.7 (20), R3.1
TDM_MCLK: R1.2, TP1.1, U1.41 (SCKI)
TDM_MCLK_T: J2.4 (23), R1.1
TDM_RX: R5.1, TP5.1, U1.8 (DOUT1)
TDM_RX_T: J1.10 (8), R5.2
TDM_TX: R4.2, TP4.1, U1.37 (DIN1)
TDM_TX_T: J1.9 (7), R4.1
USBH_DM: J3.2, U5.15 (DMU)
USBH_DP: J3.1, U5.16 (DPU)
USB_A_DM: J10.8, U5.8 (DM2), U8.3 (IO2), U8.4 (IO2)
USB_A_DP: J10.7, U5.9 (DP2), U8.1 (IO1), U8.6 (IO1)
USB_B_DM: J11.8, U5.10 (DM1), U9.3 (IO2), U9.4 (IO2)
USB_B_DP: J11.7, U5.11 (DP1), U9.1 (IO1), U9.6 (IO1)
VBAT: C102.1, J16.1, R9.1, TP15.1, U10.2 (BAT), U10.3 (BAT)
VBAT_SENSE: C1.1, J2.5 (22), R9.2, R10.1
VBUS_IN: C100.1, C119.1, D30.1 (K), J15.A9 (VBUS), J15.B9 (VBUS), R120.1, R121.1, R125.1, R134.1, U10.13 (IN), U15.12 (VDD)
VCOMAD: C19.1, R26.2, R27.2, R32.2, R33.2, R52.2, R53.2, R92.2, R93.2, U1.1 (VCOMAD)
VCOMDA: C20.1, U1.15 (VCOMDA)
VREFAD1: C21.1, U1.59 (VREFAD1)
VREFAD2: C22.1, U1.60 (VREFAD2)

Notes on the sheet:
TEENSY 4.0 SOCKETS, CLOCK SERIES R, I2C, HOST WIRES
CODEC PCM3168A (TDM slave, I2C 0x44)
HEADSET MIC PREAMP INA217
HEADSET AMP OPA1622 (DAC1 L, DAC2 R)
RADIO A: RX DIFF IN, TX DRIVER, PTT, GROUND LIFT
RADIO B: RX DIFF IN, TX DRIVER, PTT, GROUND LIFT
USB HUB FE1.1s, RADIO VBUS SWITCHES, ESD
POWER: USB-C + TUSB321 current detect, BQ24074, 18650, SWITCH, TPS61230 5.2 V BOOST
ANALOG RAILS: LM27762 +/-5 V, NCP163 5.0 V, TLV75533 3.3 V
HEADERS, AUX, TEST POINTS, MOUNTING
Notes: cut the Teensy 4.0 VUSB-VIN pad. Codec MCLK = BCLK = 256 fs (8 x 32-bit TDM): firmware MUST set SRDA/SRAD = single rate (auto mode reads 256 fs as dual rate).

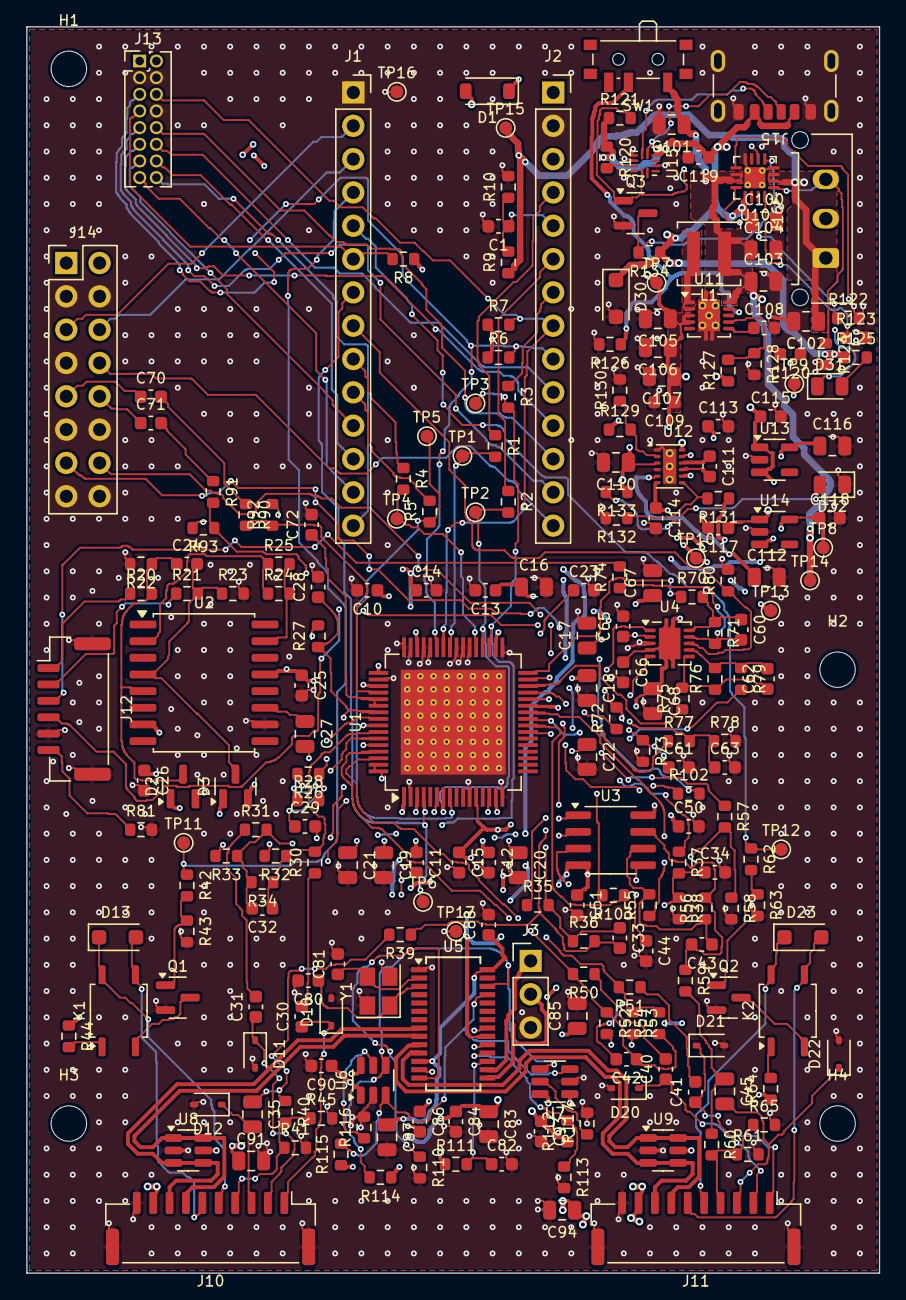
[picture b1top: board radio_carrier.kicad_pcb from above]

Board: 4 copper layers, 65.0 x 95.0 mm, 240 parts (0 on the bottom side), 155 nets.

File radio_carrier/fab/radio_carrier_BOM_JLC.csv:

Comment,Designator,Footprint,LCSC Part #
100nF,"C1,C25,C26,C50,C51,C65,C66,C82,C84,C86,C88,C90,C93",C_0603_1608Metric,C14663
1uF,"C10,C11,C12,C13,C14,C15,C23,C28,C30,C31,C40,C41,C70,C71,C72,C109,C111,C115,C117,C118,C119",C_0603_1608Metric,C15849
10uF,"C16,C17,C18,C19,C20,C21,C22,C27,C35,C45,C67,C68,C83,C85,C87,C91,C94,C101,C102,C104,C110,C112",C_0805_2012Metric,C15850
0603CG102J500NT,"C24,C32,C33,C34,C42,C43,C44",C_0603_1608Metric,C1636
0603N272J500CT,C29,C_0603_1608Metric,C388043
CL10C331JB8NNNC,"C60,C61,C62,C63",C_0603_1608Metric,C1664
4.7uF,"C100,C116",C_0805_2012Metric,C1779
22uF,"C103,C105,C106,C107",C_0805_2012Metric,C45783
10nF,C108,C_0603_1608Metric,C57112
2.2uF,"C113,C114",C_0603_1608Metric,C23630
CL10C180JB8NNNC,C120,C_0603_1608Metric,C1647
B5819W,D1,D_SOD-123,C8598
BAV99,"D2,D3",SOT-23,C2500
PESD5V0L1BA,"D10,D11,D12,D20,D21,D22",D_SOD-323,C85380
SMF15CA,"D13,D23",D_SOD-123F,C2890424
SMF5.0A,D30,D_SOD-123F,C78395
RED,D31,LED_0805_2012Metric,C84256
GREEN,D32,LED_0805_2012Metric,C2297
"Teensy 4.0 left (GND,0..12)",J1,PinSocket_1x14_P2.54mm_Vertical,
"Teensy 4.0 right (VIN,GND,3V3,23..13)",J2,PinSocket_1x14_P2.54mm_Vertical,
USB HOST (wire to Teensy pads),J3,PinHeader_1x03_P2.54mm_Vertical,
BM10B-GHS-TBT,J10,JST_GH_BM10B-GHS-TBT_1x10-1MP_P1.25mm_Vertical,C2983879
BM10B-GHS-TBT,J11,JST_GH_BM10B-GHS-TBT_1x10-1MP_P1.25mm_Vertical,C2983879
BM06B-GHS-TBT,J12,JST_GH_BM06B-GHS-TBT_1x06-1MP_P1.25mm_Vertical,C189892
FRONT PANEL (2x8 1.27),J13,PinHeader_2x08_P1.27mm_Vertical,
AUX (2x8 2.54),J14,PinHeader_2x08_P2.54mm_Vertical,
USB4125-GF-A-0190,J15,USB_C_Receptacle_GCT_USB4125-xx-x-0190_6P_TopMnt_Horizontal,C5246813
43650-0315,J16,Molex_Micro-Fit_3.0_43650-0315_1x03_P3.00mm_Vertical,
AQY212GS,"K1,K2",SOP-4_3.8x4.1mm_P2.54mm,C719745
XAL4020-102MEC,L1,L_Coilcraft_XAL4020-XXX,C4555951
2N7002,"Q1,Q2,Q3",SOT-23,C8545
33,"R1,R2,R3,R4,R5",R_0603_1608Metric,C23140
2.2k,"R6,R7,R133",R_0603_1608Metric,C4190
10k,"R8,R22,R23,R30,R31,R50,R51,R90,R91,R111,R113,R114,R115",R_0603_1608Metric,C25804
100k,"R9,R10,R26,R27,R32,R33,R43,R52,R53,R63,R80,R92,R93,R121,R128,R130,R132,R134",R_0603_1608Metric,C25803
47,"R20,R21",R_0603_1608Metric,C23182
ERJ-3EKF1690V,R24,R_0603_1608Metric,C403019
1k,"R28,R39,R42,R59,R62,R123,R125",R_0603_1608Metric,C21190
RT0603BRD0720KL,"R35,R37,R55,R57",R_0603_1608Metric,C723637
RT0603BRD074K99L,"R36,R38,R56,R58",R_0603_1608Metric,C723532
100,"R40,R60,R102,R103",R_0603_1608Metric,C22775
10,"R41,R61,R74,R79",R_0603_1608Metric,C22859
330,"R44,R64",R_0603_1608Metric,C23138
0,"R45,R65,R81",R_0603_1608Metric,C21189
RT0603BRD0715KL,"R70,R72,R75,R77",R_0603_1608Metric,C326733
TD03G1102BT,"R71,R73,R76,R78",R_0603_1608Metric,C667038
2.7k,R110,R_0603_1608Metric,C13167
4.7k,R112,R_0603_1608Metric,C23162
ARG03FTC4532,"R116,R117",R_0603_1608Metric,C218038
CR0603-FX-9103ELF,R120,R_0603_1608Metric,C203887
CRCW06031K24FKEA,R122,R_0603_1608Metric,C843923
1M,R126,R_0603_1608Metric,C22935
RTT034223FTP,R127,R_0603_1608Metric,C103627
RTT032943FTP,R129,R_0603_1608Metric,C13177
CR0603FA2873G,R131,R_0603_1608Metric,C100934
PCM12SMTR,SW1,SW_SPDT_PCM12,C221841
PCM3168APAPR,U1,HTQFP-64-1EP_10x10mm_P0.5mm_EP8x8mm_Mask4.4x4.4mm_ThermalVias,C529289
INA217AIDWR,U2,SOIC-16W_7.5x10.3mm_P1.27mm,C1849416
OPA1678IDR,U3,SOIC-8_3.9x4.9mm_P1.27mm,C192421
OPA1622IDRCR,U4,Texas_S-PVSON-N10,C2876559
FE1.1S-BSOP28BCN,U5,SSOP-28_3.9x9.9mm_P0.635mm,C9359
TPS2552DBVR,"U6,U7",SOT-23-6,C46506
USBLC6-2SC6,"U8,U9",SOT-23-6,C7519
BQ24074RGTR,U10,VQFN-16-1EP_3x3mm_P0.5mm_EP1.6x1.6mm_ThermalVias,C54313
TPS61230DRCR,U11,Texas_S-PVSON-N10_ThermalVias,C139626
LM27762DSSR,U12,WSON-12-1EP_3x2mm_P0.5mm_EP1x2.65_ThermalVias,C473398
NCP163ASN500T1G,U13,SOT-23-5,C603657
TLV75533PDBVR,U14,SOT-23-5,C404027
TUSB321RWBR,U15,Texas_X2QFN-12_1.6x1.6mm_P0.4mm,C139392
X322512MSB4SI,Y1,Crystal_SMD_3225-4Pin_3.2x2.5mm,C9002
